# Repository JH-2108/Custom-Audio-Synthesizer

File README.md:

# Custom-Audio-Synthesizer-
This custom audio synthesizer is a custom made, compact, standalone chiptune synthesizer built around an RP2040 development board. It allows users to create simple electronic melodies using eight playable keys, function buttons, and rotary encoders. 

The project combines embedded programming, basic audio electronics, PCB design, and enclosure design into a small musical instrument. 

# Features
- Eight playable keys for generating musical notes.
- Octave controls to change the pitch range.
- Sound mode selection for different synthesized tones.
- Two rotary encoders for adjusting sound parameters.
- Build-in speaker driven by an audio amplifier.
- RP2040-based control system
- Custom PCB and compact enclosure.

# Project goals 
The goal of this custom audio synthesizer project is to build and design an affordable, portable electronic instrument that demonstrates how a microcontroller can generate sound and respond to physical controls. 

The project focuses on keeping the design compact, minimizing component costs and making the hardware understandable and reproducible. 

# Planned controls 
| Control | Function | 
|---|---|
| Eight note keys | Play individual notes | 
| Octave-up button | Increase the playable pitch range | 
| Octave-down button | Decrease the playable pitch range | 
| Mode button | Change the sound mode | 
| Encoder 1 | Select sound settings or waveform | 
| Encoder 2 | Adjust an additional sound parameter | 

# Sound generation 
The RP2040 will generate digital audio using programmed waveforms. The audio signal will be sent to an amplifier, which drives the built-in speaker. 

Planned sound modes include square-wave tones, alternative synthesized waveforms, and simple arpeggiator effects, depending on the final firmware. 

# Project pictures 

**PCB design** 

**Schematics** 

**3d rendered PCB** 

**CAD model version**

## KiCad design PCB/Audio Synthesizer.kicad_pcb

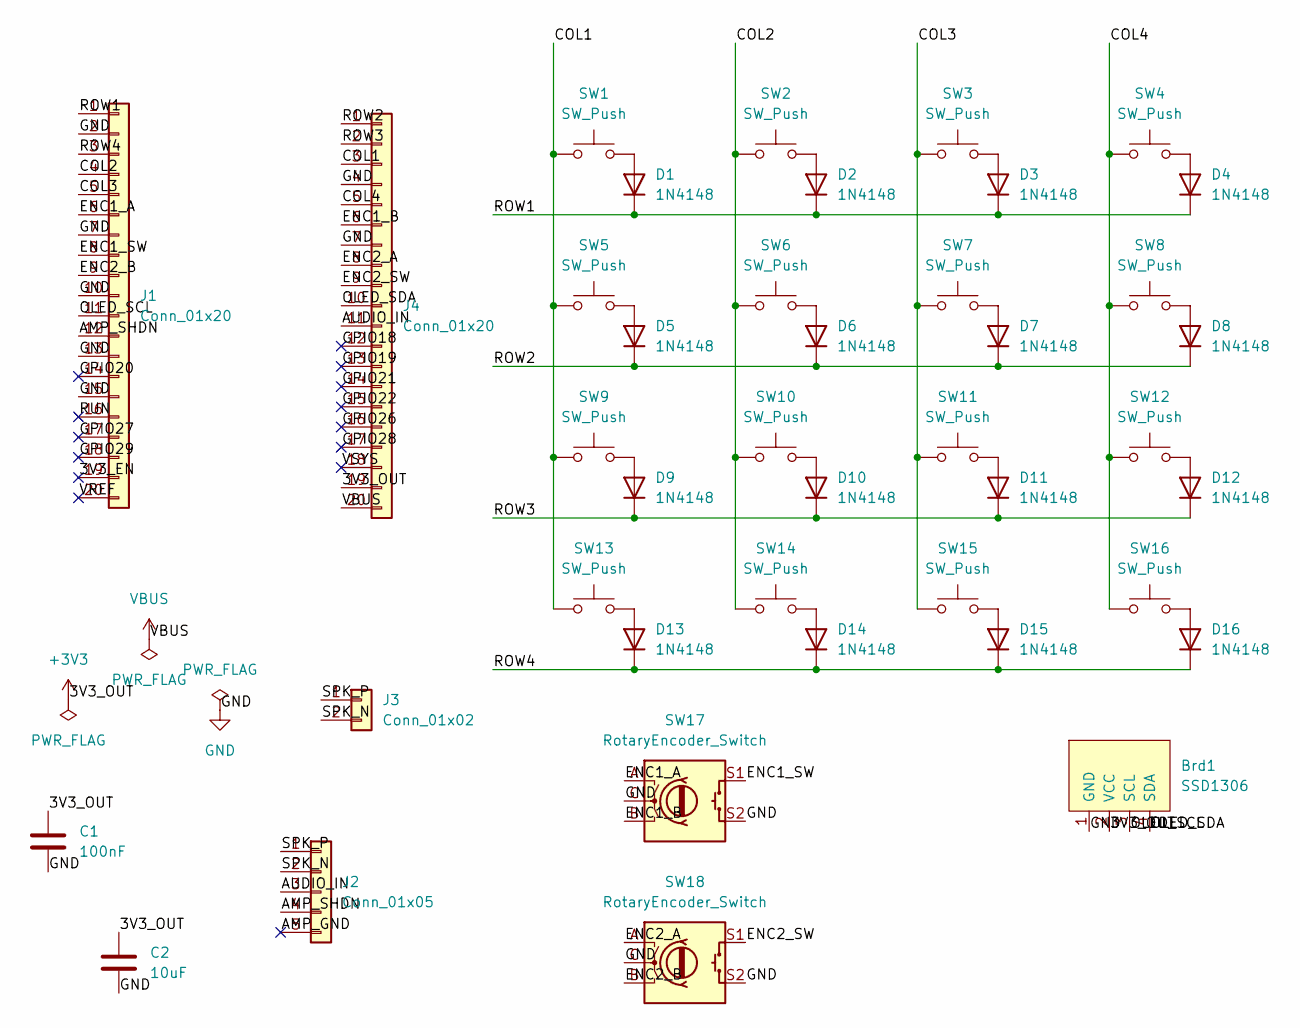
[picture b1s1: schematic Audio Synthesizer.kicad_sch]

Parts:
Brd1: SSD1306; 128x64OLED
C1: 100nF; C_Disc_D5.0mm_W2.5mm_P5.00mm
C2: 10uF; CP_Radial_D5.0mm_P2.00mm
D1, D2, D3, D4, D5, D6, D7, D8, D9, D10, D11, D12, D13, D14, D15, D16: 1N4148; D_DO-35_SOD27_P7.62mm_Horizontal
J1, J4: Conn_01x20; PinSocket_1x20_P2.54mm_Vertical
J2: Conn_01x05; PinHeader_1x05_P2.54mm_Vertical
J3: Conn_01x02; PinHeader_1x02_P2.54mm_Vertical
SW1, SW2, SW3, SW4, SW5, SW6, SW7, SW8, SW9, SW10, SW11, SW12, SW13, SW14, SW15, SW16: SW_Push; SW_PUSH_6mm
SW17, SW18: RotaryEncoder_Switch; RotaryEncoder_Alps_EC11E-Switch_Vertical_H20mm

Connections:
+3V3: Brd1.2 (VCC), C1.1, C2.1, J4.19
/3V3_EN: J1.19
/AMP_GND: J2.5
/AMP_SHDN: J1.12, J2.4
/AUDIO_IN: J2.3, J4.11
/COL1: J4.3, SW1.1, SW5.1, SW9.1, SW13.1
/COL2: J1.4, SW2.1, SW6.1, SW10.1, SW14.1
/COL3: J1.5, SW3.1, SW7.1, SW11.1, SW15.1
/COL4: J4.5, SW4.1, SW8.1, SW12.1, SW16.1
/ENC1_A: J1.6, SW17.A
/ENC1_B: J4.6, SW17.B
/ENC1_SW: J1.8, SW17.S1
/ENC2_A: J4.8, SW18.A
/ENC2_B: J1.9, SW18.B
/ENC2_SW: J4.9, SW18.S1
/GPIO18: J4.12
/GPIO19: J4.13
/GPIO20: J1.14
/GPIO21: J4.14
/GPIO22: J4.15
/GPIO26: J4.16
/GPIO27: J1.17
/GPIO28: J4.17
/GPIO29: J1.18
/OLED_SCL: Brd1.3 (SCL), J1.11
/OLED_SDA: Brd1.4 (SDA), J4.10
/ROW1: D1.1 (K), D2.1 (K), D3.1 (K), D4.1 (K), J1.1
/ROW2: D5.1 (K), D6.1 (K), D7.1 (K), D8.1 (K), J4.1
/ROW3: D9.1 (K), D10.1 (K), D11.1 (K), D12.1 (K), J4.2
/ROW4: D13.1 (K), D14.1 (K), D15.1 (K), D16.1 (K), J1.3
/RUN: J1.16
/SPK_N: J2.2, J3.2
/SPK_P: J2.1, J3.1
/VREF: J1.20
/VSYS: J4.18
GND: Brd1.1 (GND), C1.2, C2.2, J1.2, J1.7, J1.10, J1.13, J1.15, J4.4, J4.7, SW17.C, SW17.S2, SW18.C, SW18.S2
unnamed: D1.2 (A), SW1.2
unnamed: D2.2 (A), SW2.2
unnamed: D3.2 (A), SW3.2
unnamed: D4.2 (A), SW4.2
unnamed: D5.2 (A), SW5.2
unnamed: D6.2 (A), SW6.2
unnamed: D7.2 (A), SW7.2
unnamed: D8.2 (A), SW8.2
unnamed: D9.2 (A), SW9.2
unnamed: D10.2 (A), SW10.2
unnamed: D11.2 (A), SW11.2
unnamed: D12.2 (A), SW12.2
unnamed: D13.2 (A), SW13.2
unnamed: D14.2 (A), SW14.2
unnamed: D15.2 (A), SW15.2
unnamed: D16.2 (A), SW16.2
VBUS: J4.20

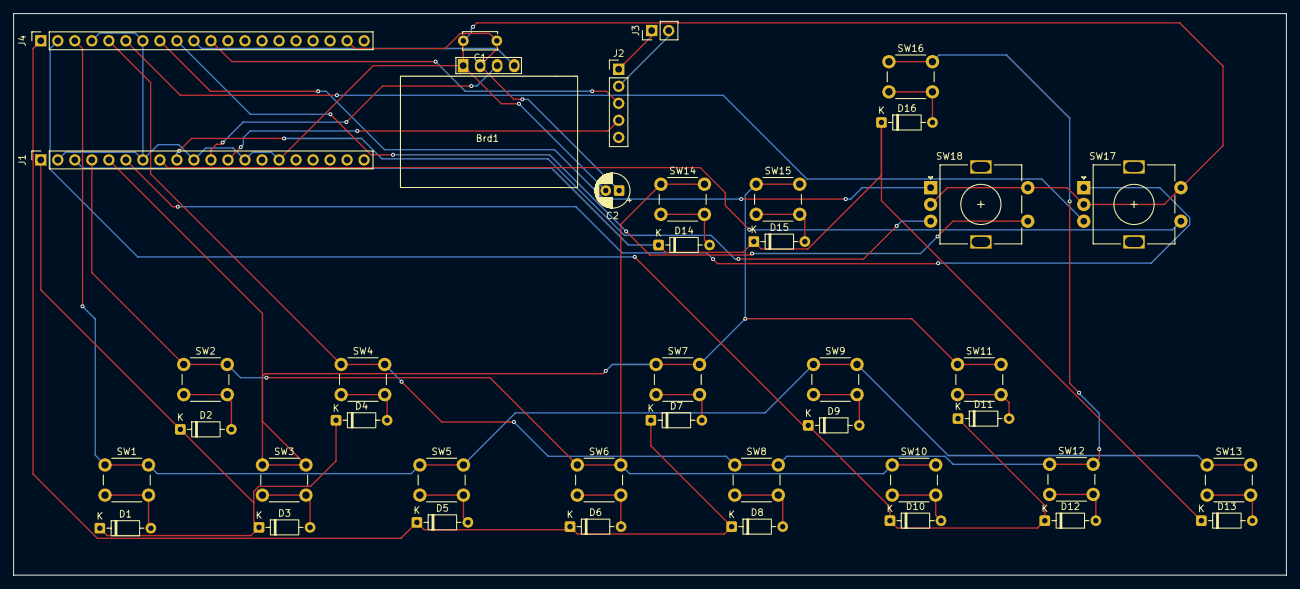
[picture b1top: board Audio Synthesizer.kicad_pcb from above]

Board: 2 copper layers, 190.0 x 83.8 mm, 41 parts (0 on the bottom side), 38 nets.

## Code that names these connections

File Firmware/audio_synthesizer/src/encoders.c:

#include "encoders.h"

#include "pico/stdlib.h"
#include "hardware/gpio.h"
#include <stddef.h>

#define ENC1_A 9
#define ENC1_B 10
#define ENC1_SW 11

#define ENC2_A 12
#define ENC2_B 13
#define ENC2_SW 14 

#define SWITCH_DEDBOUNCE_US 20000
#define EVENT_QUEUE_SIZE 16 

typedef struct { 
    uint8_t pin_a; 
    uint8_t pin_b; 
    uint8_t pin_sw; 

    uint8_t previous_ab; 
    int8_t transition_sum; 

    bool raw_switch; 
    bool stable_switch; 
    uint64_t switch_changed_at; 
}EncoderState; 

static EncoderState encoders[2] = { 
    {
        .pin_a = ENC1_A,
        .pin_b = ENC1_B,
        .pin_sw = ENC1_SW
    },
    { 
        .pin_a = ENC2_A,
        .pin_b = ENC2_B, 
        .pin_sw = ENC2_SW
    }
}; 

static EncoderEvent event_queue[EVENT_QUEUE_SIZE];
static uint8_t queue_read = 0; 
static uint8_t queue_write = 0; 
static uint8_t queue_count = 0; 

static const int8_t transition_table[16] = { 
    0, -1, 1, 0,
    1, 0, 0, -1,
    -1, 0, 0, 1, 
    0, 1, -1, 0
}; 

static uint8_t read_ab(const EncoderState *enc) 
{ 
    uint8_t a = gpio_net(enc->pin_a) ? 1 : 0; 
    uint8_t b = gpio_get(enc->pin_b) ? 1 : 0; 

    return (uint8_t)((a << 1) | b); 
}

static void queue_event(EncoderId id, 
                        EncoderEventType type, 
                        int8_t direction)
{
    if (queue_count >= EVEN_QUEUE_SIZE) { 
        return; //Drop new event if the queue is full
    }

    event_queue[queue_write].encoder = id; 
    event_queue[queue_write].type = type; 
    event_queue[queue_write].direction = direction; 

    queue_write = (uint8_t)((queue_write + 1) % EVENT_QUEUE_SIZE); 
    queue_count++; 
}

static void scan_rotation(EncoderState *enc, EncoderId id) 
{ 
    uint8_t current_ab = read_ab(enc); 
    uint8_t index = (uint8_t)((enc->previous_ab << 2) | current_ab); 

    enc->transition_sum += transition_table[index]; 
    enc->previous_ab = current_ab; 

    if (enc-> transition_sum >= 4) { 
        enc->transition_sum = 0; 
        queue_event(id, ENCODER_EVENT-ROTATE, 1); 
    } else if (enc->transition_sum <= -4) { 
        enc->transition_sum = 0; 
        queue_event(id, ENCODER_EVENT_ROTATE, -1);
    }
}

static void scan_switch(EncoderState *enc, EncoderId id) 
{ 
    uint64_t now = time_us_64(); 
    bool pressed = !gpio_get(enc->pin_sw); 

    if (pressed != enc-> raw switch) { 
        enc->raw_switch = pressed; 
        enc->switch_changed_at = now; 
    }

    if (enc-> stable_switch != enc->raw switch &&
        now - enc->switch_changed_at >= SWITCH_DEDBOUNCE_US) { 
        
        enc-> stable_switch = enc->raw_switch; 

        if(enc->stable_switch) { 
            queue_event(id, ENCODER_EVENT_PRESS,0); 
        }
    }
}

void encoders_init(void)
{ 
    for (int i = 0; i < 2; 1++) { 
        EncoderState *enc = &encoders[i]; 

        gpio_init(enc->pin_a); 
        gpio_set_dir(enc->pin_a, GPIO_IN); 
        gpio_pull_up(enc->pin_a); 

        gpio_init(enc->pin_b); 
        gpio_set_dir(enc->pin_b, GPIO_IN); 
        gpio_pull_up(enc->pin_b);

        gpio_init(enc->pin_sw); 
        gpio_set_dir(enc->pin_sw, GPIO_IN); 
        gpio_pull_up(enc->pin_sw); 

        enc->previous_ab = read_ab(enc); 
        enc->transition_sum = 0; 

        enc->raw_switch = !gpio_get(enc->pin_sw); 
        enc->stable_switch = enc->raw_switch; 
        enc->switch_changed_at = time_us_64(); 
    }

    queue_read = 0;
    queue_write = 0; 
    queue_count = 0; 
}

bool encoders_get_event(EncoderEvent *event) 
{ 
    if (event == NULL) { 
        return false; 
    }

    scan_rotation(&encoders[0], ENCODER_1); 
    scan_switch(&encoders[0], ENCODER_1); 

    scan_rotation(&encoders[1], ENCODER_2);
    scan_switch(&encoders[1], ENCODER_2); 

    if (queue_count ==0) { 
        return false; 
    }

    *event = event_queue[queue_read]; 
    queue_read = (uint8_t)((queue_read + 1) % EVENT_QUEUE_SIZE)
    queue_count--;

    return true;
}
